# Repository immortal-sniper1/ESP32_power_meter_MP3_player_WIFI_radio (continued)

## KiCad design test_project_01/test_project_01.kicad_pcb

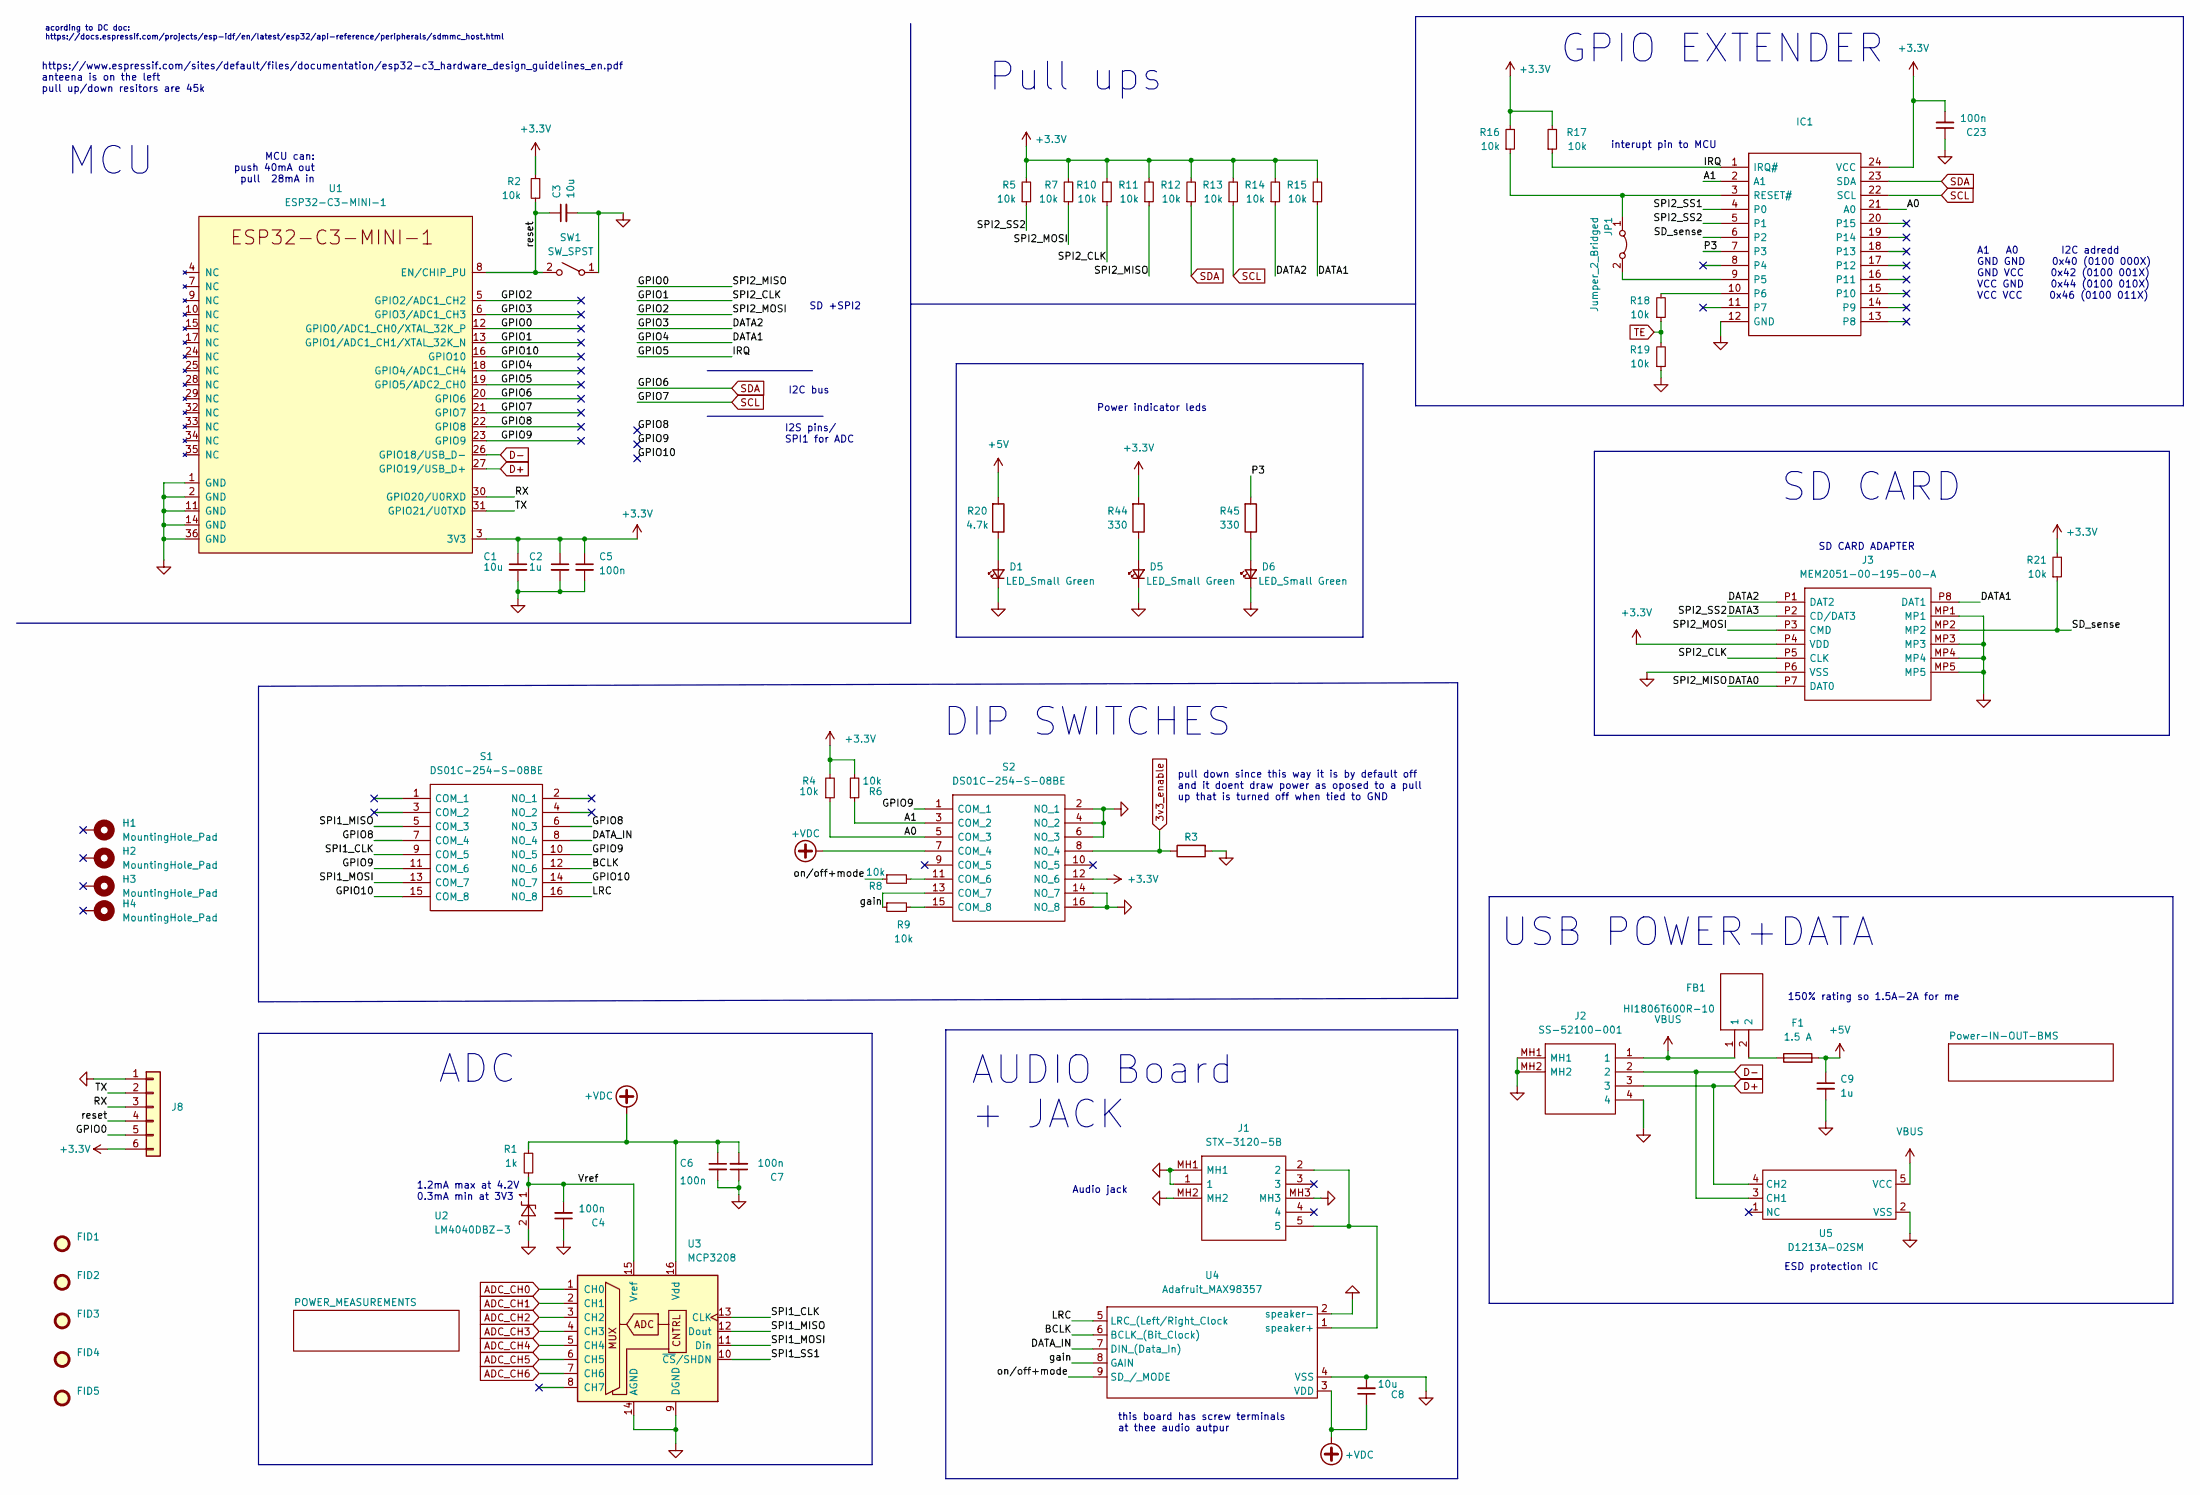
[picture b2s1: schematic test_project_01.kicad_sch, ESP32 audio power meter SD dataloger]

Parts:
C1, C3, C8: 10u; C_0603_1608Metric_Pad1.08x0.95mm_HandSolder
C2, C9: 1u; C_0603_1608Metric_Pad1.08x0.95mm_HandSolder
C4, C5, C6, C7, C23: 100n; C_0603_1608Metric_Pad1.08x0.95mm_HandSolder
D1, D5, D6: LED_Small Green; LED_0603_1608Metric_Pad1.05x0.95mm_HandSolder
F1: 1.5 A; Fuse_0603_1608Metric_Pad1.05x0.95mm_HandSolder
FB1: HI1806T600R-10; BEADC4516X185N; Mouser Part Number 875-HI1806T600R-10
FID1, FID2, FID3, FID4, FID5: (no value)
H1, H2, H3, H4: MountingHole_Pad; MountingHole_3.2mm_M3
IC1: Mouser Part Number 701-XRA1203IG24TR-F
J1: STX-3120-5B; STX31205B; Mouser Part Number 806-STX-3120-5B
J2: SS-52100-001; SS52100001; Mouser Part Number 530-SS-52100-001
J3: MEM2051-00-195-00-A; MEM20510019500A; Mouser Part Number 640-MEM20510019500A
J8: (no value)
JP1: Jumper_2_Bridged; SolderJumper-2_P1.3mm_Bridged_RoundedPad1.0x1.5mm
R1: 1k; R_0603_1608Metric_Pad0.98x0.95mm_HandSolder
R2, R4, R5, R6, R7, R8, R9, R10, R11, R12, R13, R14, R15, R16, R17, R18, R19, R21: 10k; R_0603_1608Metric_Pad0.98x0.95mm_HandSolder
R3: (no value)
R20: 4.7k; R_0805_2012Metric
R44, R45: 330; R_0603_1608Metric_Pad0.98x0.95mm_HandSolder
S1, S2: DS01C-254-S-08BE; DS01C254S08BE; Mouser Part Number 490-DS01C-254-S-08BE
SW1: SW_SPST; PTS526SM15SMTR2LFS
U1: ESP32-C3-MINI-1; ESP32-C3-MINI-1_Hand-Soldering
U2: LM4040DBZ-3; SOT-23
U3: MCP3208; SOIC-16_3.9x9.9mm_P1.27mm
U4: Adafruit_MAX98357; Adafruit MAX98357 I2S Class-D Mono
U5: D1213A-02SM; SOT-23-5

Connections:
3v3_enable: R3.1, S2.8 (NO_4); also elsewhere on the board
+5V: C9.1, F1.2, R20.2; also elsewhere on the board
+VDC: C6.1, C7.2, C8.1, R1.1, S2.7 (COM_4), U3.16 (Vdd), U4.3 (VDD); also elsewhere on the board
/A0: IC1.21 (A0), R4.1, S2.5 (COM_3)
/A1: IC1.2 (A1), R6.1, S2.3 (COM_2)
/BCLK: S1.12 (NO_6), U4.6 (BCLK_(Bit_Clock))
/DATA0: J3.P7 (DAT0), J8.5, R11.1, U1.12 (GPIO0/ADC1_CH0/XTAL_32K_P)
/DATA1: J3.P8 (DAT1), R15.1, U1.18 (GPIO4/ADC1_CH4)
/DATA2: J3.P1 (DAT2), R14.1, U1.6 (GPIO3/ADC1_CH3)
/DATA3: IC1.5 (P1), J3.P2 (CD/DAT3), R5.1
/DATA_IN: S1.8 (NO_4), U4.7 (DIN_(Data_In))
/GPIO1: J3.P5 (CLK), R10.1, U1.13 (GPIO1/ADC1_CH1/XTAL_32K_N)
/GPIO2: J3.P3 (CMD), R7.1, U1.5 (GPIO2/ADC1_CH2)
/GPIO5: IC1.1 (IRQ#), R17.1, U1.19 (GPIO5/ADC2_CH0)
/GPIO8: S1.6 (NO_3), S1.7 (COM_4), U1.22 (GPIO8)
/GPIO9: S1.10 (NO_5), S1.11 (COM_6), S2.1 (COM_1), U1.23 (GPIO9)
/GPIO10: S1.14 (NO_7), S1.15 (COM_8), U1.16 (GPIO10)
/LRC: S1.16 (NO_8), U4.5 (LRC_(Left/Right_Clock)
/P3: IC1.7 (P3), R45.2
/RX: J8.3, U1.30 (GPIO20/U0RXD)
/SD_sense: IC1.6 (P2), J3.MP2, R21.1
/SPI1_CLK: S1.9 (COM_5), U3.13 (CLK)
/SPI1_MISO: S1.5 (COM_3), U3.12 (Dout)
/SPI1_MOSI: S1.13 (COM_7), U3.11 (Din)
/SPI1_SS1: U3.10 (~CS/SHDN)
/SPI2_SS1: IC1.4 (P0)
/TX: J8.2, U1.31 (GPIO21/U0TXD)
/Vref: C4.2, R1.2, U2.1 (K), U3.15 (Vref)
/gain: R9.1, S2.13 (COM_7), U4.8 (GAIN)
/on/off+mode: R8.1, U4.9 (SD_/_MODE)
/reset: C3.1, J8.4, R2.2, SW1.2 (B), U1.8 (EN/CHIP_PU)
ADC_CH0: U3.1 (CH0); also elsewhere on the board
ADC_CH1: U3.2 (CH1); also elsewhere on the board
ADC_CH2: U3.3 (CH2); also elsewhere on the board
ADC_CH3: U3.4 (CH3); also elsewhere on the board
ADC_CH4: U3.5 (CH4); also elsewhere on the board
ADC_CH5: U3.6 (CH5); also elsewhere on the board
ADC_CH6: U3.7 (CH6); also elsewhere on the board
D+: J2.3, U1.27 (GPIO19/USB_D+), U5.4 (CH2)
D-: J2.2, U1.26 (GPIO18/USB_D-), U5.3 (CH1)
GND: C1.2, C2.2, C3.2, C4.1, C5.2, C6.2, C7.1, C8.2, C9.2, C23.1, D1.1 (K), D5.1 (K), D6.1 (K), IC1.12 (GND), J1.1, J1.MH1, J1.MH2, J1.MH3, J2.4, J2.MH1, J2.MH2, J3.MP1, J3.MP3, J3.MP4, J3.MP5, J3.P6 (VSS), J8.1, R3.2, R19.1, S2.2 (NO_1), S2.4 (NO_2), S2.6 (NO_3), S2.14 (NO_7), S2.16 (NO_8), SW1.1 (A), U1.1 (GND), U1.2 (GND), U1.11 (GND), U1.14 (GND), U1.36 (GND), U2.2 (A), U3.9 (DGND), U3.14 (AGND), U4.2 (speaker-), U4.4 (VSS), U5.2 (VSS); also elsewhere on the board
unnamed: D1.2 (A), R20.1
unnamed: D5.2 (A), R44.1
unnamed: D6.2 (A), R45.1
unnamed: F1.1, FB1.2
unnamed: IC1.3 (RESET#), JP1.1 (A), R16.1
unnamed: IC1.9 (P5), JP1.2 (B)
unnamed: IC1.10 (P6), R18.2
unnamed: J1.2, J1.5, U4.1 (speaker+)
unnamed: R8.2, S2.11 (COM_6)
unnamed: R9.2, S2.15 (COM_8)
SCL: IC1.22 (SCL), R13.1, U1.21 (GPIO7)
SDA: IC1.23 (SDA), R12.1, U1.20 (GPIO6)
TE: R18.1, R19.2; also elsewhere on the board
VBUS: FB1.1, J2.1, U5.5 (VCC)

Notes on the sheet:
Pull ups
AUDIO Board + JACK
interupt pin to MCU
SD CARD ADAPTER
MCU can: push 40mA out pull 28mA in
https://www.espressif.com/sites/default/files/documentation/esp32-c3_hardware_design_guidelines_en.pdf anteena is on the left pull up/down resitors are 45k
DIP SWITCHES
I2S pins/ SPI1 for ADC
pull down since this way it is by default off and it doent draw power as oposed to a pull up that is turned off when tied to GND
Power indicator leds
150% rating so 1.5A-2A for me
ESD protection IC
A1 A0 I2C adredd GND GND 0x40 (0100 000X) GND VCC 0x42 (0100 001X) VCC GND 0x44 (0100 010X) VCC VCC 0x46 (0100 011X)
GPIO EXTENDER
SD CARD
USB POWER+DATA
ADC
SD +SPI2
I2C bus
acording to DC doc: https://docs.espressif.com/projects/esp-idf/en/latest/esp32/api-reference/peripherals/sdmmc_host.html
1.2mA max at 4.2V 0.3mA min at 3V3
Audio jack
this board has screw terminals at thee audio autpur
MCU

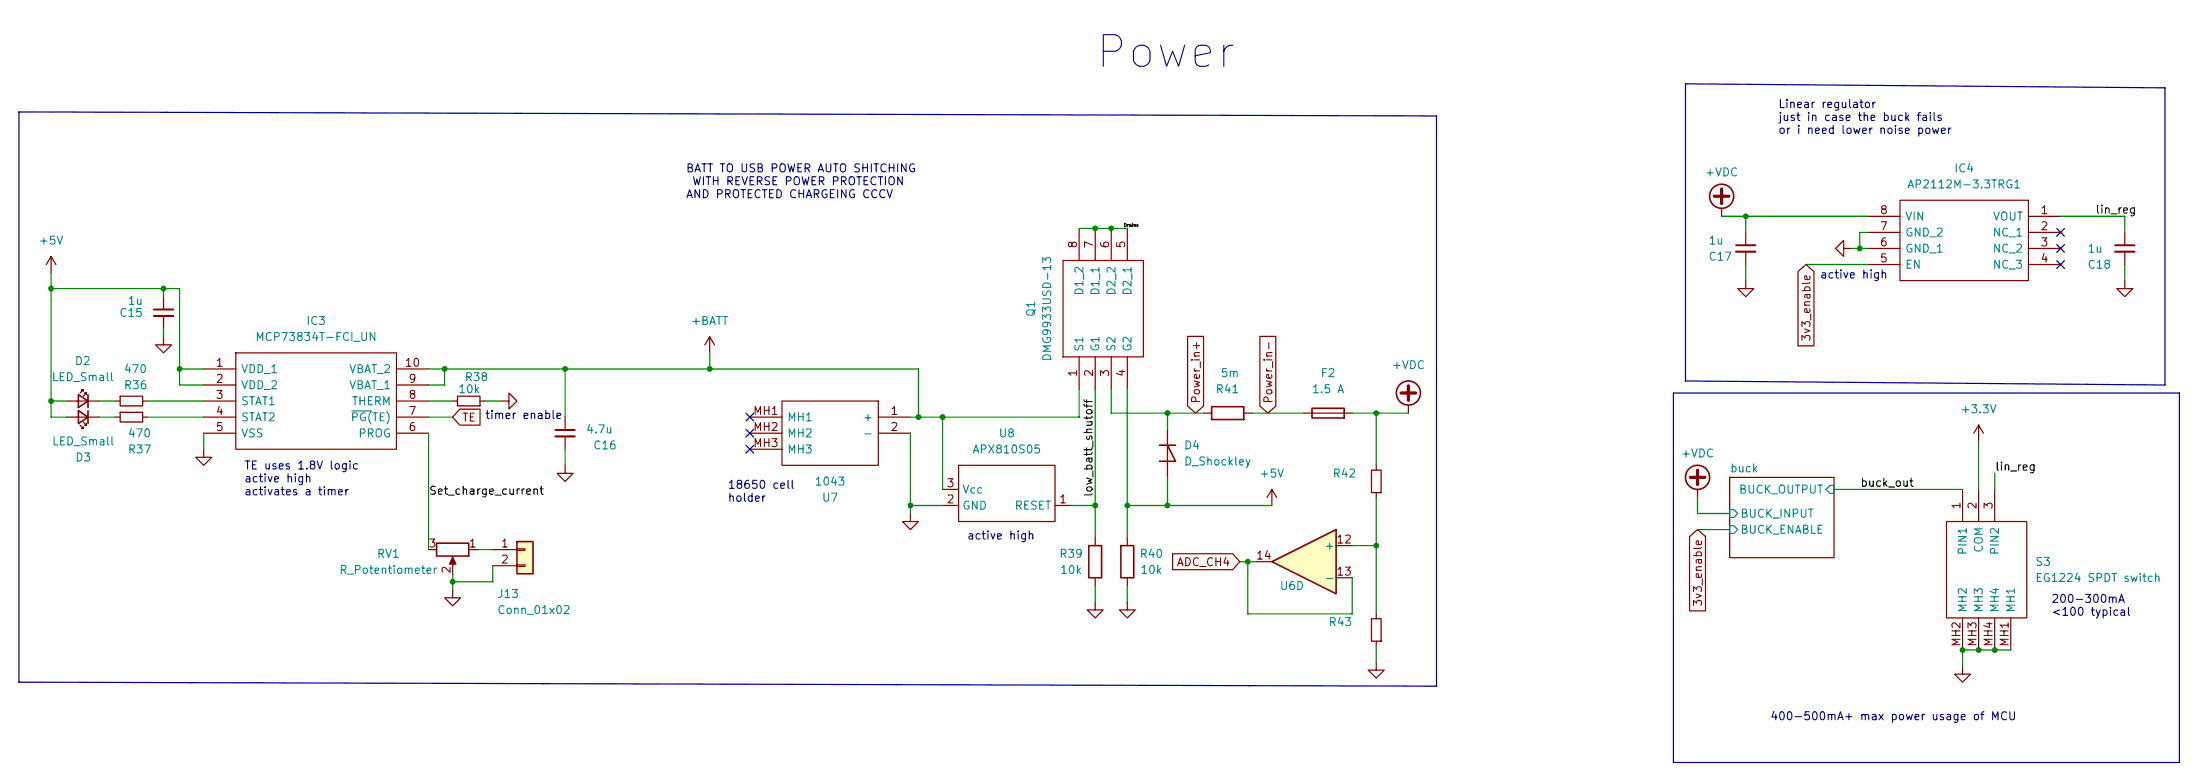
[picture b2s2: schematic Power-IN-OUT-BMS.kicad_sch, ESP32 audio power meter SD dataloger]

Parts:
C15: 1u; C_0603_1608Metric_Pad1.08x0.95mm_HandSolder
C16: 4.7u; C_0603_1608Metric_Pad1.08x0.95mm_HandSolder
C17, C18: 1u; C_0805_2012Metric_Pad1.18x1.45mm_HandSolder
D2, D3: LED_Small; LED_0603_1608Metric_Pad1.05x0.95mm_HandSolder
D4: D_Shockley; D_DO-15_P5.08mm_Vertical_AnodeUp
F2: 1.5 A; Fuse_0603_1608Metric_Pad1.05x0.95mm_HandSolder
IC3: MCP73834T-FCI_UN; SOP50P490X110-10N; Mouser Part Number 579-MCP73834T-FCI/UN
IC4: AP2112M-3.3TRG1; SOIC127P600X170-8N; Mouser Part Number 621-AP2112M-3.3TRG1
J13: Conn_01x02; PinHeader_1x02_P2.54mm_Vertical
Q1: DMG9933USD-13; SOIC127P600X175-8N; Mouser Part Number 621-DMG9933USD-13
R36, R37: 470; R_0603_1608Metric_Pad0.98x0.95mm_HandSolder
R38, R39, R40: 10k; R_0603_1608Metric_Pad0.98x0.95mm_HandSolder
R41: 5m; R_0612_1632Metric_Pad1.18x3.40mm_HandSolder
R42, R43: (no value)
RV1: R_Potentiometer; Potentiometer_Bourns_3386F_Vertical
S3: EG1224 SPDT switch; EG1224; Mouser Part Number 612-EG1224
U6: (no value)
U7: 1043; Mouser Part Number 534-1043
U8: APX810S05; SOT-23

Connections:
3v3_enable: IC4.5 (EN); also elsewhere on the board
+5V: C15.1, D2.2 (A), D3.2 (A), D4.2 (A), IC3.1 (VDD_1), IC3.2 (VDD_2), Q1.4 (G2), R40.2; also elsewhere on the board
+BATT: C16.1, IC3.9 (VBAT_1), IC3.10 (VBAT_2), Q1.1 (S1), U7.1 (+), U8.3 (Vcc)
+VDC: C17.1, F2.2, IC4.8 (VIN), R42.2; also elsewhere on the board
/Power-IN-OUT-BMS/Drains: Q1.5 (D2_1), Q1.6 (D2_2), Q1.7 (D1_1), Q1.8 (D1_2)
/Power-IN-OUT-BMS/Set_charge_current: IC3.6 (PROG), RV1.3
/Power-IN-OUT-BMS/buck_out: S3.1 (PIN1); also elsewhere on the board
/Power-IN-OUT-BMS/lin_reg: C18.1, IC4.1 (VOUT), S3.3 (PIN2)
/Power-IN-OUT-BMS/low_batt_shutoff: Q1.2 (G1), R39.2, U8.1 (RESET)
ADC_CH4: U6.13 (-), U6.14; also elsewhere on the board
GND: C15.2, C16.2, C17.2, C18.2, IC3.5 (VSS), IC4.6 (GND_1), IC4.7 (GND_2), J13.2, R38.1, R39.1, R40.1, R43.1, RV1.2, S3.MH1, S3.MH2, S3.MH3, S3.MH4, U7.2 (-), U8.2 (GND); also elsewhere on the board
unnamed: D2.1 (K), R36.1
unnamed: D3.1 (K), R37.1
unnamed: IC3.3 (STAT1), R36.2
unnamed: IC3.4 (STAT2), R37.2
unnamed: IC3.8 (THERM), R38.2
unnamed: J13.1, RV1.1
unnamed: R42.1, R43.2, U6.12 (+)
Power_in+: D4.1 (K), Q1.3 (S2), R41.1; also elsewhere on the board
Power_in-: F2.1, R41.2; also elsewhere on the board
TE: IC3.7 (~PG(TE)); also elsewhere on the board

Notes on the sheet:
400-500mA+ max power usage of MCU
active high
timer enable
TE uses 1.8V logic active high activates a timer
Linear regulator just in case the buck fails or i need lower noise power
Power
BATT TO USB POWER AUTO SHITCHING WITH REVERSE POWER PROTECTION AND PROTECTED CHARGEING CCCV
18650 cell holder
200-300mA <100 typical

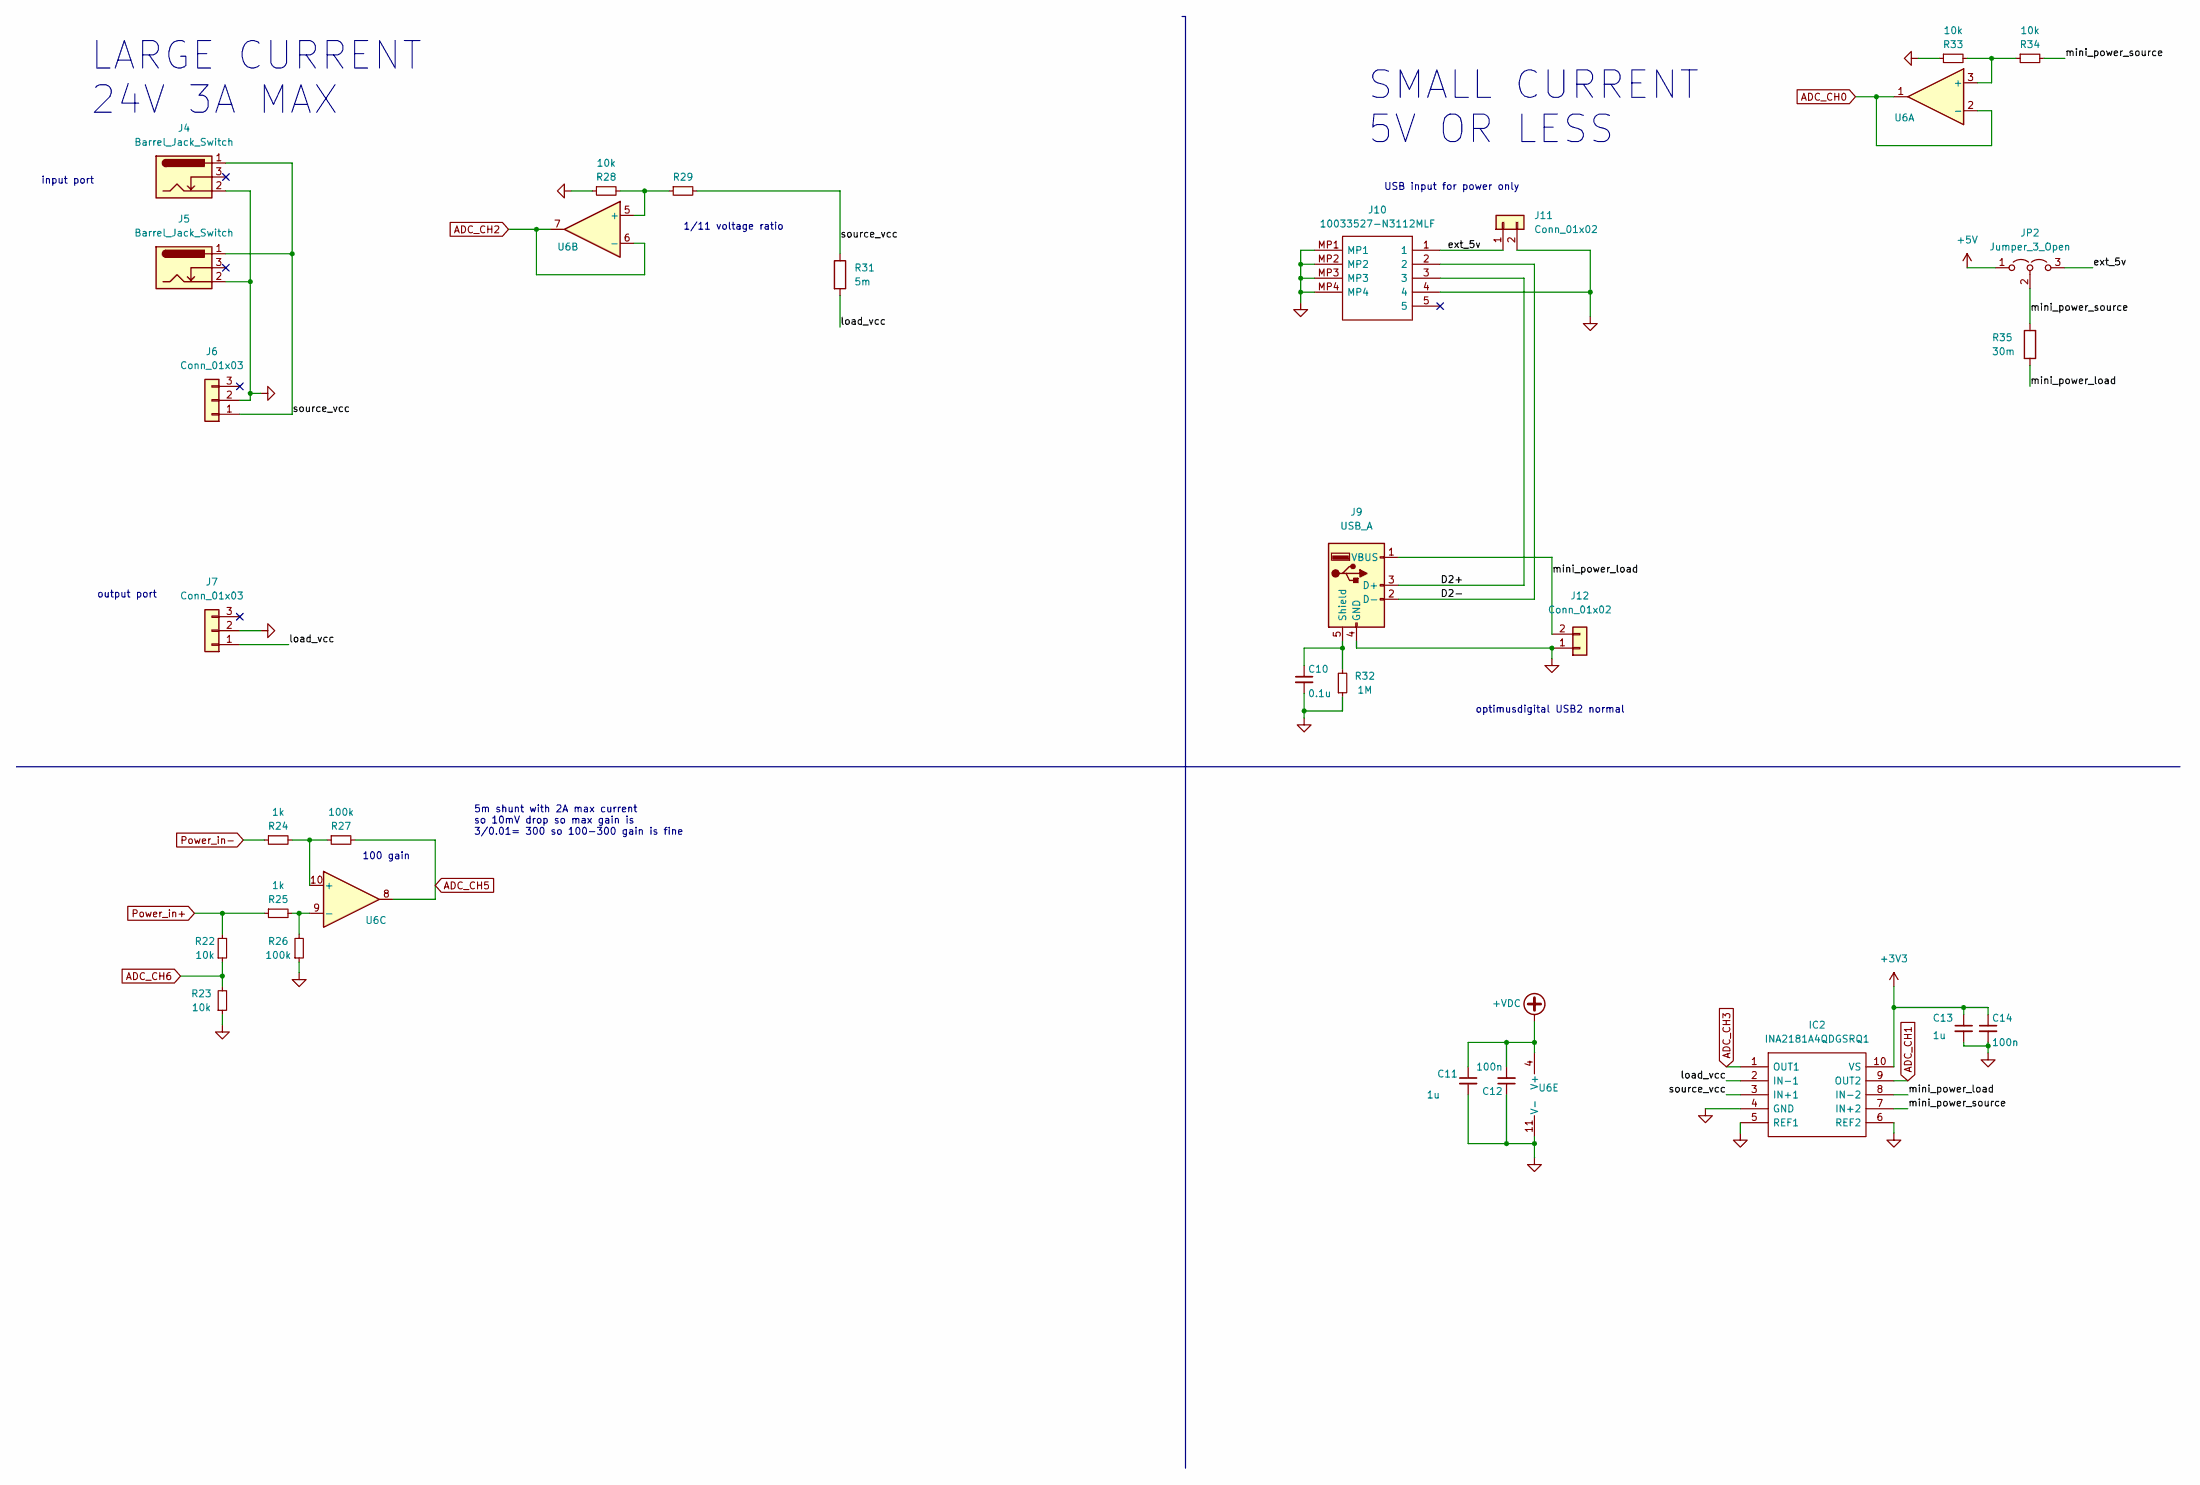
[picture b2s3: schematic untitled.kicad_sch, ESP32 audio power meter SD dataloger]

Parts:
C10: 0.1u; C_0603_1608Metric_Pad1.08x0.95mm_HandSolder
C11, C13: 1u; C_0603_1608Metric_Pad1.08x0.95mm_HandSolder
C12, C14: 100n; C_0603_1608Metric_Pad1.08x0.95mm_HandSolder
IC2: INA2181A4QDGSRQ1; SOP50P490X110-10N; Mouser Part Number 595-INA2181A4QDGSRQ1
J4: Barrel_Jack_Switch; DC plug jack 5.5-2.5mm
J5: Barrel_Jack_Switch; BarrelJack_Wuerth_6941xx301002
J6, J7: Conn_01x03; SCREWTERMINAL-5MM-3
J9: USB_A; USB_A_Molex_67643_Horizontal
J10: 10033527-N3112MLF; 10033527N3112MLF; Mouser Part Number 649-10033527N3112MLF
J11, J12: Conn_01x02; TestPoint_2Pads_Pitch5.08mm_Drill1.3mm
JP2: Jumper_3_Open; PinHeader_1x03_P2.54mm_Vertical
R22, R23, R28, R33, R34: 10k; R_0603_1608Metric_Pad0.98x0.95mm_HandSolder
R24, R25: 1k; R_0603_1608Metric_Pad0.98x0.95mm_HandSolder
R26, R27: 100k; R_0603_1608Metric_Pad0.98x0.95mm_HandSolder
R29: (no value)
R31: 5m; R_0612_1632Metric_Pad1.18x3.40mm_HandSolder
R32: 1M; R_0603_1608Metric_Pad0.98x0.95mm_HandSolder
R35: 30m; R_0402_1005Metric_Pad0.72x0.64mm_HandSolder
U6: (no value)

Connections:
+5V: JP2.1 (A); also elsewhere on the board
+VDC: C11.1, C12.2, U6.4 (V+); also elsewhere on the board
/POWER_MEASUREMENTS/D2+: J9.3 (D+), J10.3
/POWER_MEASUREMENTS/D2-: J9.2 (D-), J10.2
/POWER_MEASUREMENTS/ext_5v: J10.1, J11.1, JP2.3 (B)
/POWER_MEASUREMENTS/load_vcc: IC2.2 (IN-1), J7.1, R31.2
/POWER_MEASUREMENTS/mini_power_load: IC2.8 (IN-2), J9.1 (VBUS), J12.2, R35.1
/POWER_MEASUREMENTS/mini_power_source: IC2.7 (IN+2), JP2.2 (C), R34.2, R35.2
/POWER_MEASUREMENTS/source_vcc: IC2.3 (IN+1), J4.1, J5.1, J6.1, R29.2, R31.1
ADC_CH0: U6.1, U6.2 (-); also elsewhere on the board
ADC_CH1: IC2.9 (OUT2); also elsewhere on the board
ADC_CH2: U6.6 (-), U6.7; also elsewhere on the board
ADC_CH3: IC2.1 (OUT1); also elsewhere on the board
ADC_CH5: R27.2, U6.8; also elsewhere on the board
ADC_CH6: R22.1, R23.2; also elsewhere on the board
GND: C10.2, C11.2, C12.1, C13.2, C14.2, IC2.4 (GND), IC2.5 (REF1), IC2.6 (REF2), J4.2, J5.2, J6.2, J7.2, J9.4 (GND), J10.4, J10.MP1, J10.MP2, J10.MP3, J10.MP4, J11.2, J12.1, R23.1, R26.1, R28.1, R32.1, R33.1, U6.11 (V-); also elsewhere on the board
unnamed: C10.1, J9.5 (Shield), R32.2
unnamed: R24.2, R27.1, U6.10 (+)
unnamed: R25.2, R26.2, U6.9 (-)
unnamed: R28.2, R29.1, U6.5 (+)
unnamed: R33.2, R34.1, U6.3 (+)
Power_in+: R22.2, R25.1; also elsewhere on the board
Power_in-: R24.1; also elsewhere on the board

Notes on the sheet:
USB input for power only
100 gain
SMALL CURRENT 5V OR LESS
1/11 voltage ratio
input port
5m shunt with 2A max current so 10mV drop so max gain is 3/0.01= 300 so 100-300 gain is fine
output port
LARGE CURRENT 24V 3A MAX
optimusdigital USB2 normal

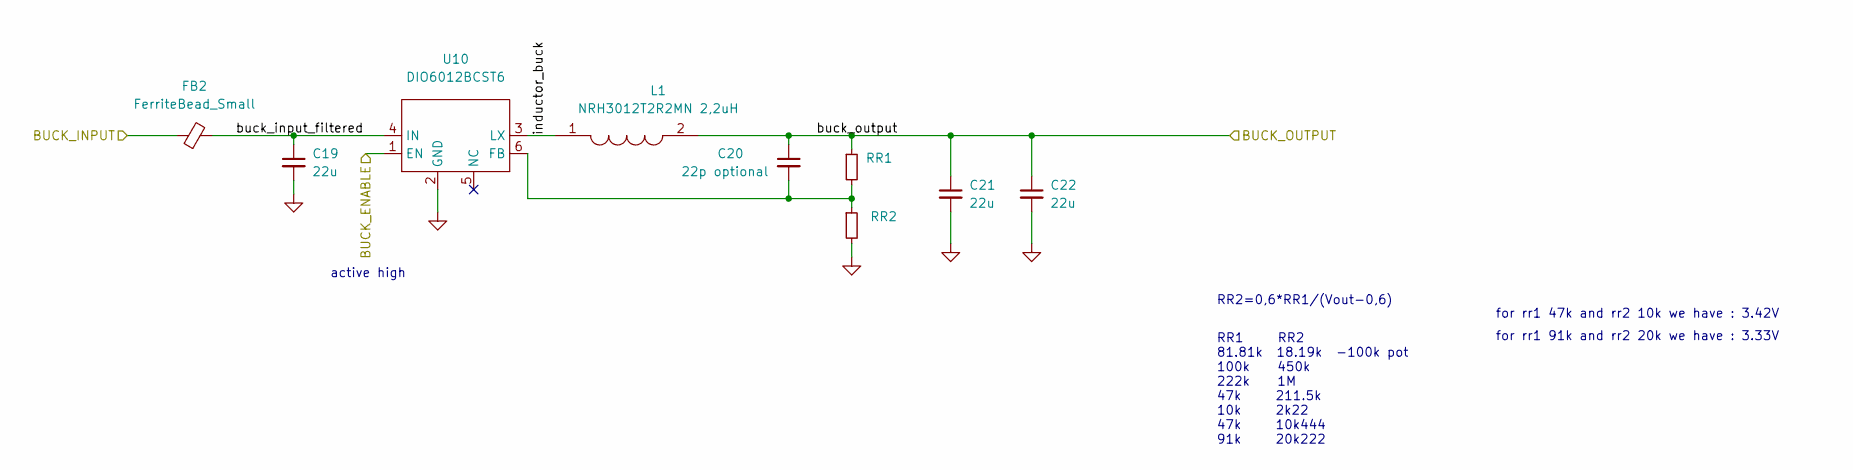
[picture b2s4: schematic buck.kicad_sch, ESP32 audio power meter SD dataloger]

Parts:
C19, C21, C22: 22u; CP_Radial_D5.0mm_P2.00mm
C20: 22p optional; C_0603_1608Metric_Pad1.08x0.95mm_HandSolder
FB2: FerriteBead_Small; R_0402_1005Metric_Pad0.72x0.64mm_HandSolder
L1: NRH3012T2R2MN 2,2uH; NRH3012T220MNV; Mouser Part Number 963-NRH3012T2R2MN
RR1, RR2: (no value)
U10: DIO6012BCST6; SOT-23-6_Handsoldering

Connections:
3v3_enable: U10.1 (EN); also elsewhere on the board
+VDC: FB2.1; also elsewhere on the board
/Power-IN-OUT-BMS/buck/buck_input_filtered: C19.1, FB2.2, U10.4 (IN)
/Power-IN-OUT-BMS/buck/inductor_buck: L1.1, U10.3 (LX)
/Power-IN-OUT-BMS/buck_out: C20.1, C21.1, C22.1, L1.2, RR1.1; also elsewhere on the board
GND: C19.2, C21.2, C22.2, RR2.2, U10.2 (GND); also elsewhere on the board
unnamed: C20.2, RR1.2, RR2.1, U10.6 (FB)

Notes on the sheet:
for rr1 47k and rr2 10k we have : 3.42V
for rr1 91k and rr2 20k we have : 3.33V
RR2=0,6*RR1/(Vout-0,6)
active high
RR1 RR2 81.81k 18.19k -100k pot 100k 450k 222k 1M 47k 211.5k 10k 2k22 47k 10k444 91k 20k222

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
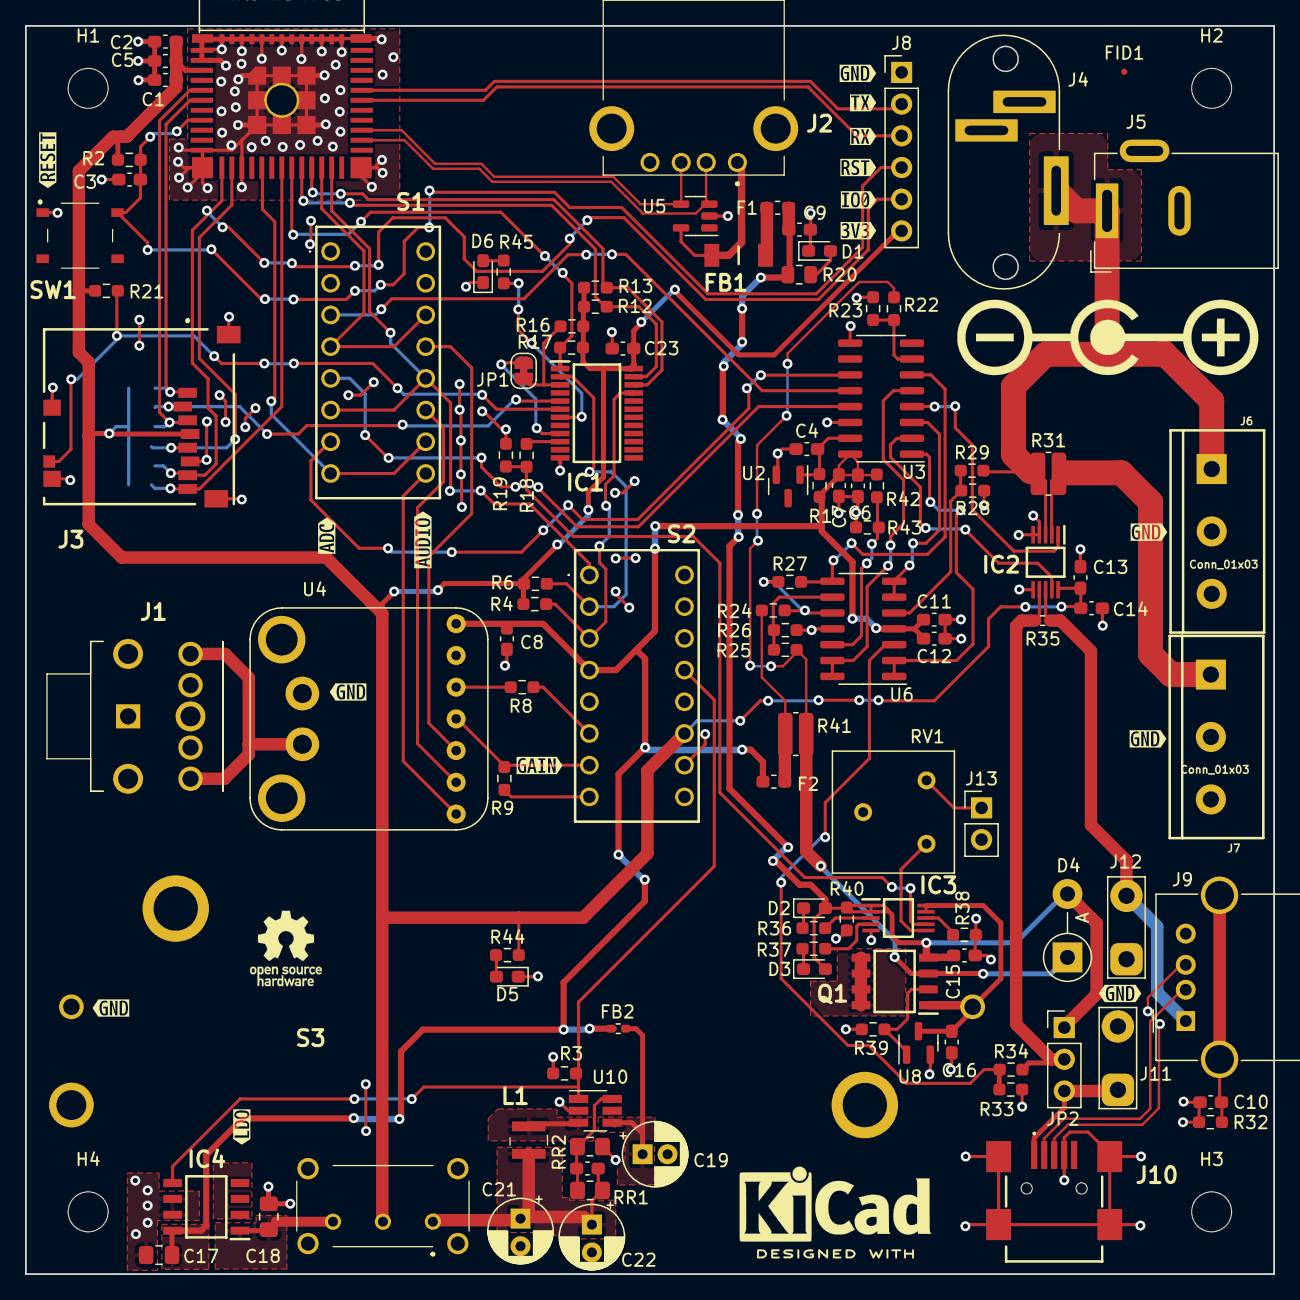
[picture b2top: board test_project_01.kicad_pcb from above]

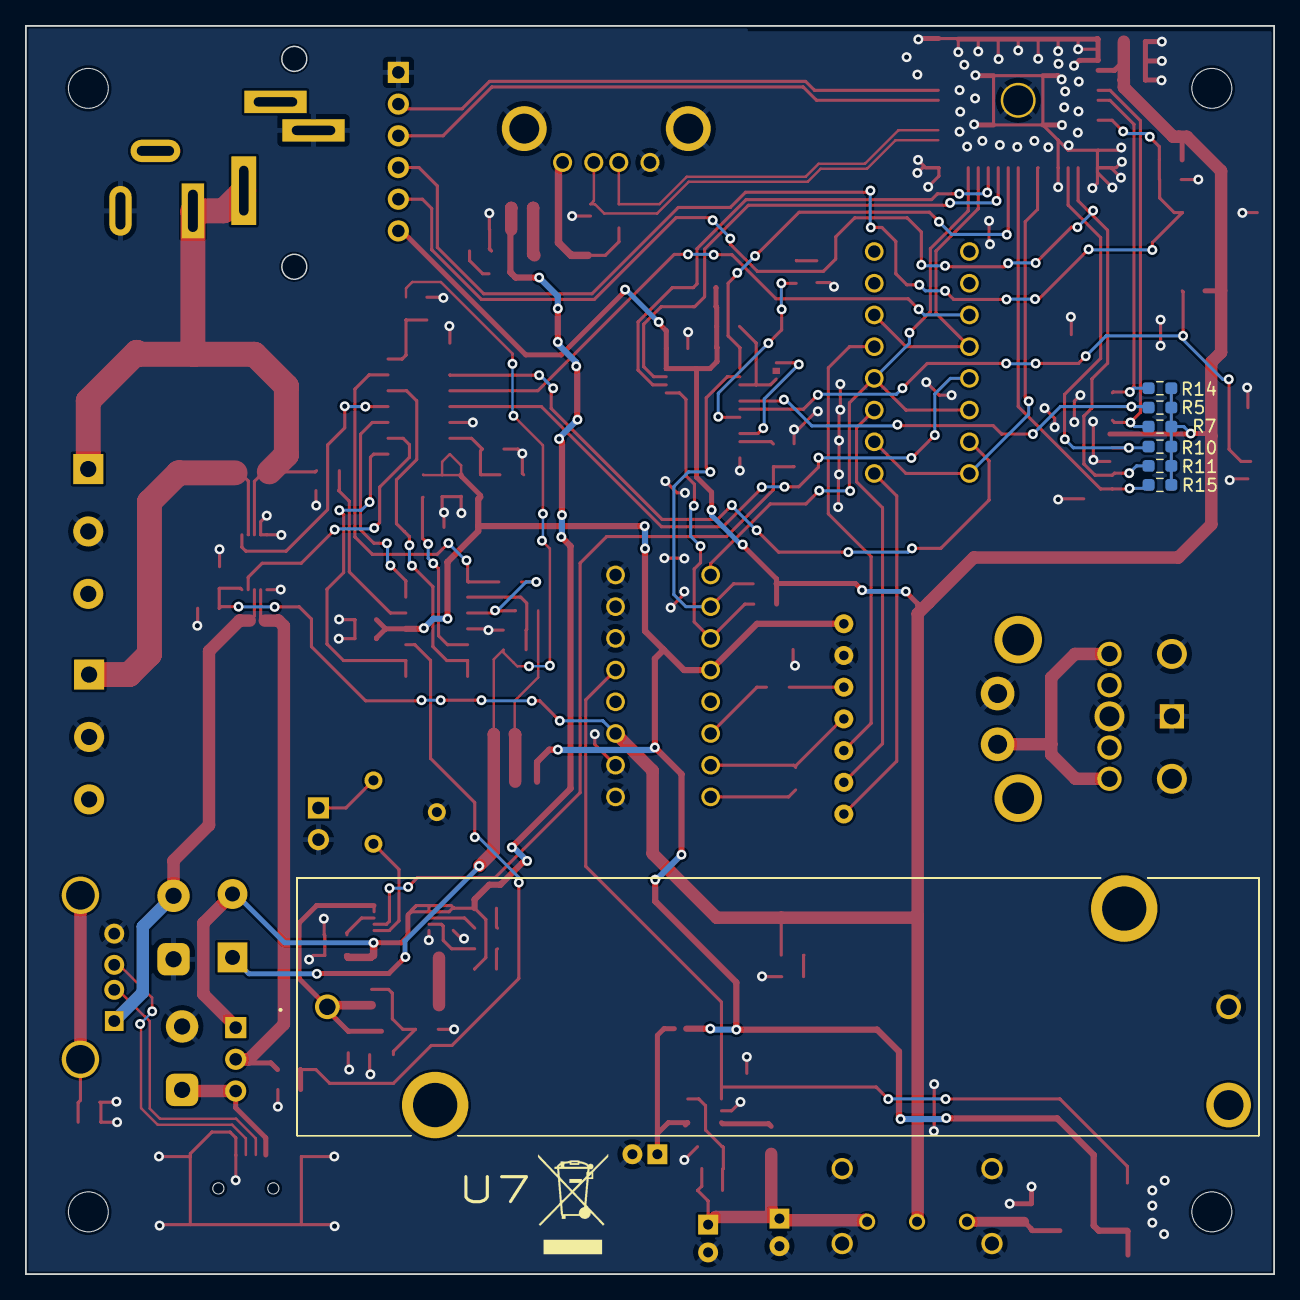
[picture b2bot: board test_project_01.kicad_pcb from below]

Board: 2 copper layers, 100.0 x 100.0 mm, 139 parts (8 on the bottom side), 84 nets.

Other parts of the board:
kibuzzard-62BCC6A1, kibuzzard-62BCC6A1#2: G***; kibuzzard-62BCC6A1
kibuzzard-62BCC6D2, kibuzzard-62BCC6D2#2, kibuzzard-62BCC6D2#3: G***; kibuzzard-62BCC6D2
kibuzzard-62BCC6DA: G***; kibuzzard-62BCC6DA
kibuzzard-62BCC6E5: G***; kibuzzard-62BCC6E5
kibuzzard-62BCC6EE: G***; kibuzzard-62BCC6EE
kibuzzard-62BCC6FB: G***; kibuzzard-62BCC6FB
kibuzzard-62BCC557: G***; kibuzzard-62BCC557
kibuzzard-62BCC581: G***; kibuzzard-62BCC581
kibuzzard-62BCC683: G***; kibuzzard-62BCC683
kibuzzard-62BCC715: G***; kibuzzard-62BCC715
kibuzzard-62BCCB31: G***; kibuzzard-62BCCB31
kibuzzard-62BCCBA4: G***; kibuzzard-62BCCBA4
kibuzzard-62BCCBB0: G***; kibuzzard-62BCCBB0

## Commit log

2022-12-02 nameing
2022-12-02 ordered and labeled versions
2022-12-24 Update fp-info-cache
